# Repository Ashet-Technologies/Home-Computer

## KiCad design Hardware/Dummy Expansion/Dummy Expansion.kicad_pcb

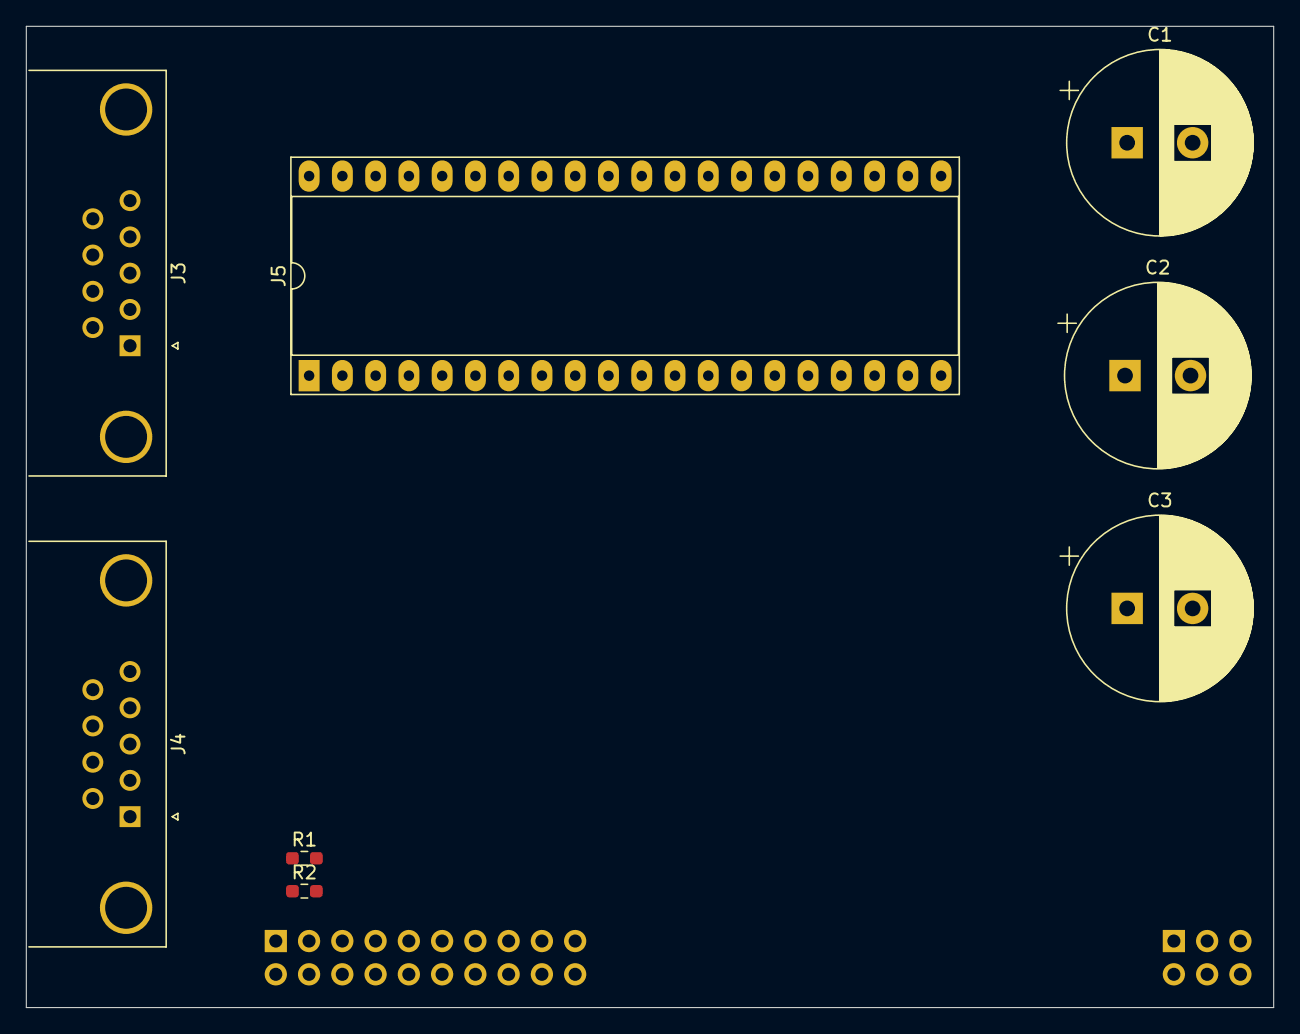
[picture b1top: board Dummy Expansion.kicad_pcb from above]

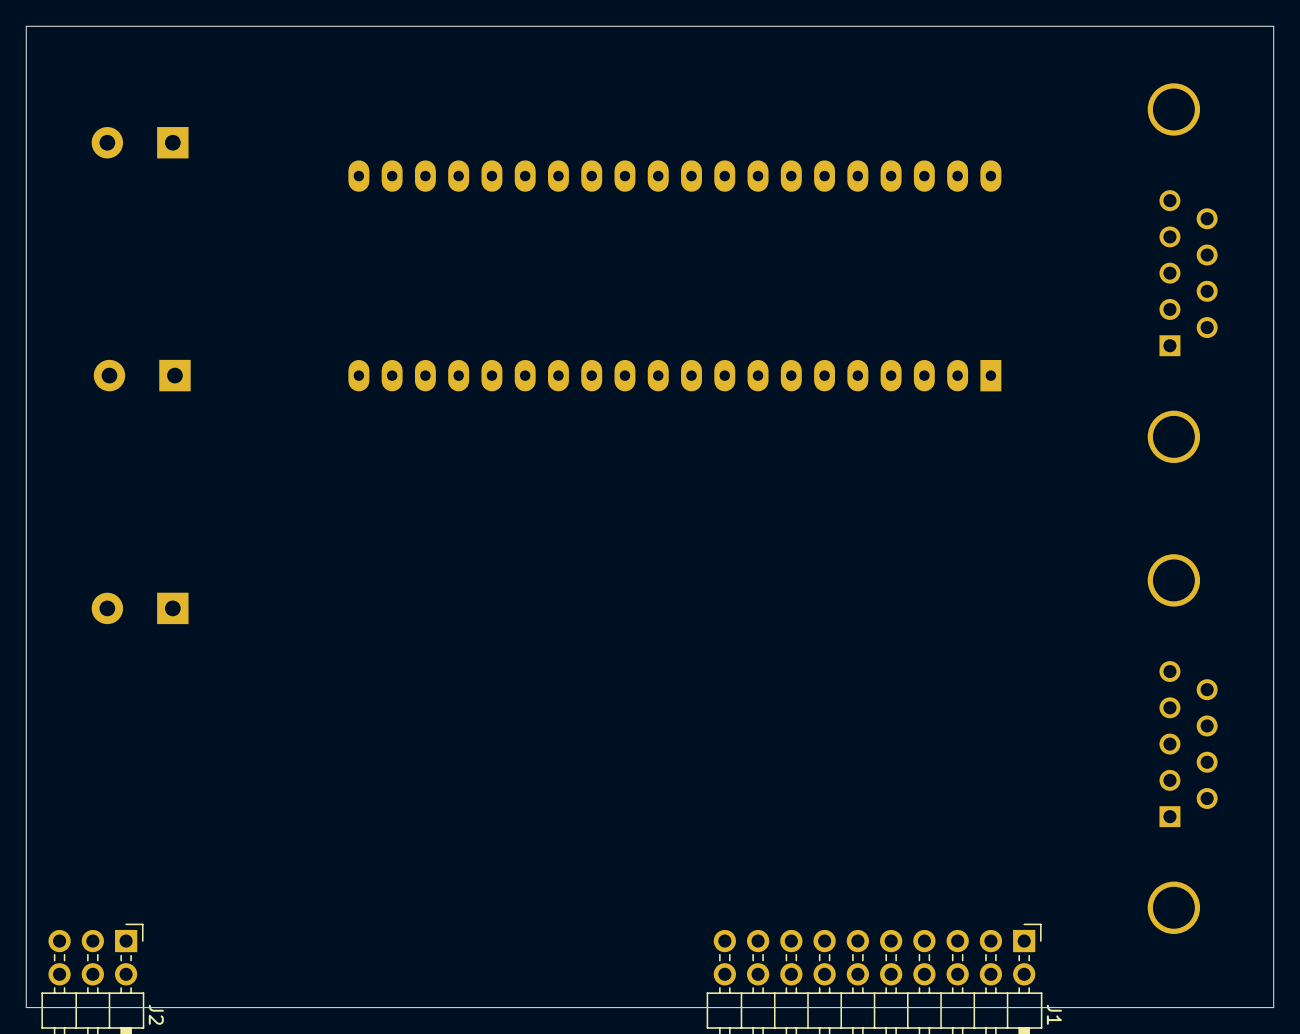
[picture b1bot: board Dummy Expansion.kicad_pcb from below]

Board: 2 copper layers, 95.2 x 74.9 mm, 10 parts (2 on the bottom side), 4 nets, no tracks yet.

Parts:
C1, C2, C3: C; CP_Radial_D14.0mm_P5.00mm
J1: Conn_02x10_Odd_Even; PinHeader_2x10_P2.54mm_Horizontal
J2: Conn_02x03_Counter_Clockwise; PinHeader_2x03_P2.54mm_Horizontal
J3, J4: DE9_Receptacle_MountingHoles; DSUB-9_Female_Horizontal_P2.77x2.84mm_EdgePinOffset4.94mm_H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
J5: Conn_02x20_Odd_Even; DIP-40_W15.24mm_Socket_LongPads
R1, R2: 10K; R_0603_1608Metric_Pad0.98x0.95mm_HandSolder

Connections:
+3V3: J1.19, R1.1, R2.1
/I2C_{SCL}: J1.4, R2.2
/I2C_{SDA}: J1.6, R1.2
GND: J1.2, J1.20, J2.1, J2.2, J2.3, J2.4, J2.5, J2.6

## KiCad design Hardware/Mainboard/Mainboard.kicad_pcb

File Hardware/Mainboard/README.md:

# Ashet Home Computer Mainboard

## Overview

- RP2350B as main CPU
- RP2350B as a debug probe
- Two 16 MiB flash chips
- 12 MHz Crystal for debug probe
- 4-port USB 1.1 HUB
- 10/100 Base-T/TX ethernet through ENC424J600
- 8 MB PSRAM (APS6404L-SQH-SN)
- 1.8V LDO for QSPI_IOVDD / PSRAM / Flash Chips

## Design Notes

- Attach debug probe to global I²S bus for both sniffing and controlling the system
- Debug probe must be able to reset the main CPU
- Debug probe can additionally drive global CLOCK_48MHZ so we can run the mainboard standalone without backplane
- Drive main CPU from CLOCK_48MHZ
- Drive debug probe through dedicated crystal
- Evaluate if debug probe can trigger the main cpu "boot over serial"
- Attach debug probe to main cpu flash directly
- Main CPU cannot be programmed through USB/UF2, but only through the debug probe
  - This must be as convenient as possible

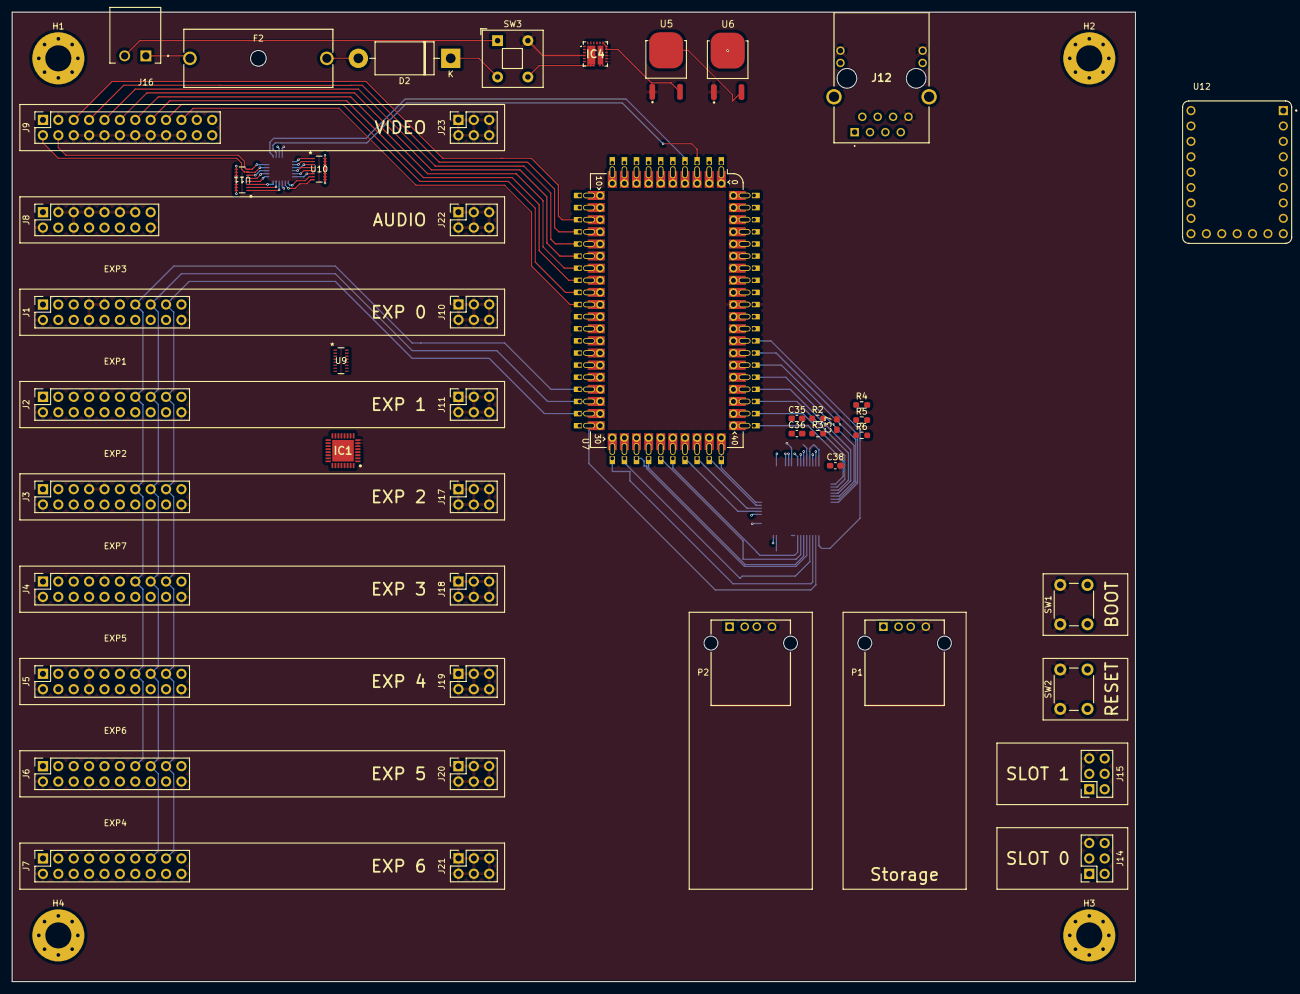
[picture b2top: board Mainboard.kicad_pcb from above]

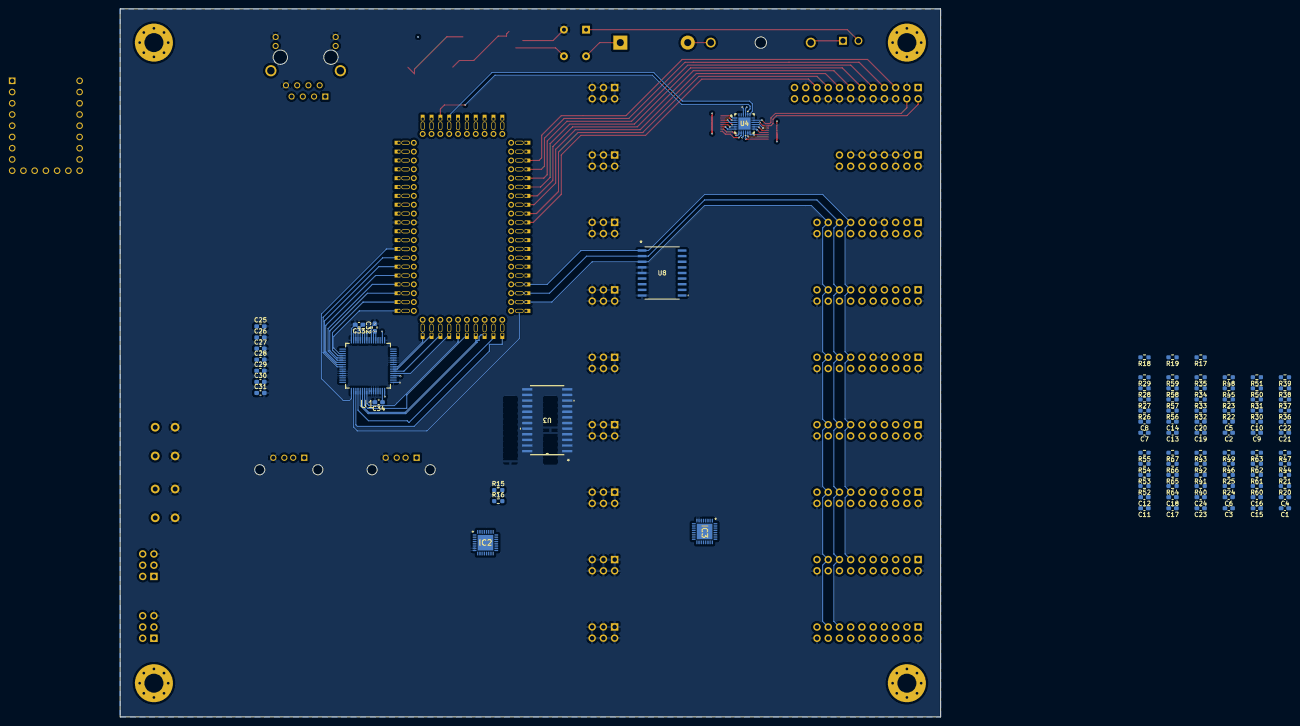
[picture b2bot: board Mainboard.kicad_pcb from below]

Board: 4 copper layers, 185.4 x 160.0 mm, 151 parts (93 on the bottom side), 159 nets.

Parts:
C1, C2, C3, C4, C5, C6, C7, C8, C9, C10, C11, C12, C13, C14, C15, C16, C17, C18, C19, C20, C21, C22, C23, C24: 22pF; C_0603_1608Metric_Pad1.08x0.95mm_HandSolder
C25, C26, C27, C28, C29, C30, C31: 100n; C_0603_1608Metric_Pad1.08x0.95mm_HandSolder
C32, C33: 1n; C_0603_1608Metric_Pad1.08x0.95mm_HandSolder
C34: 10uF; C_0603_1608Metric_Pad1.08x0.95mm_HandSolder
C35, C36: 6.8nF 10%; C_0603_1608Metric_Pad1.08x0.95mm_HandSolder
C37, C38: 10n; C_0603_1608Metric_Pad1.08x0.95mm_HandSolder
D2: 1N5822; D_DO-201AD_P15.24mm_Horizontal
EXP1, EXP2, EXP3, EXP4, EXP5, EXP6, EXP7: Expansion Card Preview
F2: 696107003002
H1, H2, H3, H4: MountingHole; MountingHole_4.3mm_M4_Pad_Via
IC1, IC2, IC3: TUSB2046BIRHBR
IC4: AOZ2261NQI-11; aoz2261ngl-11
J1, J2, J3, J4, J5, J6, J7: Conn_02x10_Odd_Even; PinSocket_2x10_P2.54mm_Vertical
J8: Conn_02x08_Odd_Even; PinSocket_2x08_P2.54mm_Vertical
J9: Conn_02x12_Odd_Even; PinSocket_2x12_P2.54mm_Vertical
J10, J11, J17, J18, J19, J20, J21, J22, J23: Conn_02x03_Counter_Clockwise; PinSocket_2x03_P2.54mm_Vertical
J12: ARJM11D7-009-AB-EW2
J14, J15: Conn_02x03_Odd_Even; PinSocket_2x03_P2.54mm_Vertical
J16: 1844210; combicon-1844210
P1, P2: USB-A1HSW6
R2, R3, R4, R5: 49.9 1%; R_0603_1608Metric_Pad0.98x0.95mm_HandSolder
R6: 10 1/12W 1%; R_0603_1608Metric_Pad0.98x0.95mm_HandSolder
R15, R16, R17, R18, R19: 10K; R_0603_1608Metric_Pad0.98x0.95mm_HandSolder
R20, R21, R22, R23, R24, R25, R26, R27, R30, R31, R32, R33, R36, R37, R40, R41, R52, R53, R56, R57, R60, R61, R64, R65: 27; R_0603_1608Metric_Pad0.98x0.95mm_HandSolder
R28, R29, R34, R35, R38, R39, R42, R43, R44, R45, R46, R47, R48, R49, R50, R51, R54, R55, R58, R59, R62, R63, R66, R67: 15K; R_0603_1608Metric_Pad0.98x0.95mm_HandSolder
SW1, SW2: SW_Push_Dual; SW_PUSH_6mm_H4.3mm
SW3: SW_DPST; SW_Push_2P1T_Toggle_CK_PVA1xxH1xxxxxxV2
U1: ENC624J600-I/PT; ENC624J600-I_PT
U3: CD74HC154M96
U4: TCA9548A; TCA9548ARGERQ1
U5, U6: AZ1084CD-3.3TRG1; AZ1084CD-3_3TRG1
U7: RP2350_Stamp_XL; RP2xxx_Stamp_XL_FlexyPin
U8: MCP23S08T-E/SO; MCP23S08T-E_SO
U9, U10, U11: YC248-JR-0710KL
U12: rp2040-zero

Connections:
+3V3: C25.1, C26.1, C27.1, C28.1, C29.1, C30.1, C31.1, C32.1, C33.1, IC1.3 (VCC_1), IC1.10 (~OVRCUR), IC1.14 (~OVRCUR2), IC1.18 (~OVRCUR3), IC1.22 (~OVRCUR4), IC1.25 (VCC_2), IC1.26 (~EXTMEM), IC2.3 (VCC_1), IC2.10 (~OVRCUR), IC2.14 (~OVRCUR2), IC2.18 (~OVRCUR3), IC2.22 (~OVRCUR4), IC2.25 (VCC_2), IC2.26 (~EXTMEM), IC3.3 (VCC_1), IC3.10 (~OVRCUR), IC3.14 (~OVRCUR2), IC3.18 (~OVRCUR3), IC3.22 (~OVRCUR4), IC3.25 (VCC_2), IC3.26 (~EXTMEM), J1.19, J2.7, J2.19, J3.8, J3.19, J4.7, J4.8, J4.19, J5.9, J5.19, J6.7, J6.9, J6.19, J7.8, J7.9, J7.19, J8.1, J9.1, J14.2, J15.2, R6.2, R15.1, R16.1, R17.1, R18.1, R19.1, U1.4 (VDDOSC), U1.18 (PSPCFG3), U1.21 (VDD_2), U1.22 (VDDPLL), U1.25 (VDDRX), U1.28 (VDDTX), U1.47 (VDD_3), U1.64 (VDD), U3.24 (VCC), U4.21 (VCC), U6.2 (VO), U8.6 (~RESET), U8.18 (VDD), U9.9 (R8), U9.10 (R7), U9.11 (R6), U9.12 (R5), U9.13 (R4), U9.14 (R3), U9.15 (R2), U9.16 (R1), U10.9 (R8), U10.10 (R7), U10.11 (R6), U10.12 (R5), U10.13 (R4), U10.14 (R3), U10.15 (R2), U10.16 (R1), U11.9 (R8), U11.10 (R7), U11.11 (R6), U11.12 (R5), U11.13 (R4), U11.14 (R3), U11.15 (R2), U11.16 (R1)
+5V: J1.1, J2.1, J3.1, J4.1, J5.1, J6.1, J7.1, J8.15, J9.23, J14.4, J15.4, P1.1 (VBUS), P2.1 (VBUS), U5.2 (VO), U6.3 (VI), U7.33 (5V), U12.23 (5V)
+6V: IC4.16 (LX_3), IC4.17 (LX_4), IC4.18 (LX_5), U5.3 (VI)
/DBG_{RXD}: U7.2 (GPIO1), U12.5 (GP4)
/DBG_{TXD}: U7.1 (GPIO0), U12.6 (GP5)
/Debug Subsystem/PROBE_SWCLK: U7.38 (SWCLK), U12.4 (GP3)
/Debug Subsystem/PROBE_SWDIO: U7.37 (SWDIO), U12.3 (GP2)
/Debug Subsystem/~BOOT: SW1.2, U7.40 (BOOTSEL)
/Debug Subsystem/~RESET: SW2.2, U7.39 (~RESET)
/Ethernet/ETH_{RX+}: C35.1, R2.1, U1.26 (TPIN+)
/Ethernet/ETH_{RX-}: C36.2, R3.1, U1.27 (TPIN-)
/Ethernet/ETH_{TX+}: J12.1 (TD+), R4.1, U1.30 (TPOUT+)
/Ethernet/ETH_{TX-}: J12.2 (TD-), R5.2, U1.31 (TPOUT-)
/Ethernet/PSP_{AD0}: U1.53 (AD0), U7.43 (GPIO32)
/Ethernet/PSP_{AD1}: U1.54 (AD1), U7.44 (GPIO33)
/Ethernet/PSP_{AD2}: U1.55 (AD2), U7.45 (GPIO34)
/Ethernet/PSP_{AD3}: U1.56 (AD3), U7.46 (GPIO35)
/Ethernet/PSP_{AD4}: U1.5 (AD4), U7.47 (GPIO36)
/Ethernet/PSP_{AD5}: U1.6 (AD5), U7.48 (GPIO37)
/Ethernet/PSP_{AD6}: U1.7 (AD6), U7.49 (GPIO38)
/Ethernet/PSP_{AD7}: U1.8 (AD7), U7.50 (GPIO39)
/Ethernet/PSP_{AD8}: U1.35 (AD8), U7.51 (GPIO40)
/Ethernet/PSP_{AD9}: U1.36 (AD9), U7.52 (GPIO41)
/Ethernet/PSP_{AD10}: U1.37 (AD10), U7.53 (GPIO42)
/Ethernet/PSP_{AD11}: U1.38 (AD11), U7.54 (GPIO43)
/Ethernet/PSP_{AD12}: U1.39 (AD12), U7.55 (GPIO44)
/Ethernet/PSP_{AD13}: U1.40 (AD13), U7.56 (GPIO45)
/Ethernet/PSP_{AD14}: U1.41 (AD14), U7.57 (GPIO46)
/Ethernet/PSP_{AL}: U1.52 (SCK/AL/PSPCFG4), U7.42 (GPIO31)
/Ethernet/PSP_{CS}: U1.49 (~CS/CS), U7.58 (GPIO47)
/Ethernet/PSP_{RD}: U1.51 (SI/RD/R~W), U7.41 (GPIO30)
/Ethernet/PSP_{WR}: U1.50 (SO/WR/WRL/EN/BOSEL), U7.30 (GPIO29)
/Expansion Subsystem/D0_{D+}: IC1.1 (DP0), R57.1, R58.2
/Expansion Subsystem/D0_{D-}: IC1.2 (DM0), R56.1, R59.2
/Expansion Subsystem/D1_{D+}: IC3.1 (DP0), R33.1, R34.2
/Expansion Subsystem/I2C0_{SCL}: U4.2 (SC0), U10.2 (R2)
/Expansion Subsystem/I2C0_{SDA}: U4.1 (SD0), U10.1 (R1)
/Expansion Subsystem/I2C1_{SCL}: U4.4 (SC1), U10.4 (R4)
/Expansion Subsystem/I2C1_{SDA}: U4.3 (SD1), U10.3 (R3)
/Expansion Subsystem/I2C2_{SCL}: U4.6 (SC2), U10.6 (R6)
/Expansion Subsystem/I2C2_{SDA}: U4.5 (SD2), U10.5 (R5)
/Expansion Subsystem/I2C3_{SCL}: U4.8 (SC3), U10.8 (R8)
/Expansion Subsystem/I2C3_{SDA}: U4.7 (SD3), U10.7 (R7)
/Expansion Subsystem/I2C4_{SCL}: U4.11 (SC4), U11.2 (R2)
/Expansion Subsystem/I2C4_{SDA}: U4.10 (SD4), U11.1 (R1)
/Expansion Subsystem/I2C5_{SCL}: U4.13 (SC5), U11.4 (R4)
/Expansion Subsystem/I2C5_{SDA}: U4.12 (SD5), U11.3 (R3)
/Expansion Subsystem/I2C6_{SCL}: U4.14 (SD6), U11.5 (R5)
/Expansion Subsystem/I2C6_{SDA}: U4.15 (SC6), U11.6 (R6)
/Expansion Subsystem/IRQ_{0}: J1.10, U8.10 (GP0), U9.8 (R8)
/Expansion Subsystem/IRQ_{1}: J2.10, U8.11 (GP1), U9.7 (R7)
/Expansion Subsystem/IRQ_{2}: J3.10, U8.12 (GP2), U9.6 (R6)
/Expansion Subsystem/IRQ_{3}: J4.10, U8.13 (GP3), U9.5 (R5)
/Expansion Subsystem/IRQ_{4}: J5.10, U8.14 (GP4), U9.4 (R4)
/Expansion Subsystem/IRQ_{5}: J6.10, U8.15 (GP5), U9.3 (R3)
/Expansion Subsystem/IRQ_{6}: J7.10, U8.16 (GP6), U9.2 (R2)
/Expansion Subsystem/IRQ_{7}: U8.17 (GP7), U9.1 (R1)
/Expansion Subsystem/SPI_{CS0}: J1.11, U3.2 (~Y1)
/Expansion Subsystem/SPI_{CS1}: J1.12, U3.3 (~Y2)
/Expansion Subsystem/SPI_{CS2}: J2.11, U3.4 (~Y3)
/Expansion Subsystem/SPI_{CS3}: J2.12, U3.5 (~Y4)
/Expansion Subsystem/SPI_{CS4}: J3.11, U3.6 (~Y5)
/Expansion Subsystem/SPI_{CS5}: J3.12, U3.7 (~Y6)
/Expansion Subsystem/SPI_{CS6}: J4.11, U3.8 (~Y7)
/Expansion Subsystem/SPI_{CS7}: J4.12, U3.9 (~Y8)
/Expansion Subsystem/SPI_{CS8}: J5.11, U3.10 (~Y9)
/Expansion Subsystem/SPI_{CS9}: J5.12, U3.11 (~Y10)
/Expansion Subsystem/SPI_{CS10}: J6.11, U3.13 (~Y11)
/Expansion Subsystem/SPI_{CS11}: J6.12, U3.14 (~Y12)
/Expansion Subsystem/SPI_{CS12}: J7.11, U3.15 (~Y13)
/Expansion Subsystem/SPI_{CS13}: J7.12, U3.16 (~Y14), U3.17 (~Y15), U8.7 (~CS)
/Expansion Subsystem/USB0_{D+}: J1.3, R60.1, R63.2
/Expansion Subsystem/USB0_{D-}: J1.5, R61.1, R62.2
/Expansion Subsystem/USB1_{D+}: J2.3, R36.1, R39.2
/Expansion Subsystem/USB1_{D-}: J2.5, R37.1, R38.2
/Expansion Subsystem/USB2_{D+}: J3.3, R30.1, R51.2
/Expansion Subsystem/USB2_{D-}: J3.5, R31.1, R50.2
/Expansion Subsystem/USB3_{D+}: J4.3, R20.1, R47.2
/Expansion Subsystem/USB3_{D-}: J4.5, R21.1, R44.2
/Expansion Subsystem/USB4_{D+}: J5.3, R64.1, R67.2
/Expansion Subsystem/USB4_{D-}: J5.5, R65.1, R66.2
/Expansion Subsystem/USB5_{D+}: J6.3, R40.1, R43.2
/Expansion Subsystem/USB5_{D-}: J6.5, R41.1, R42.2
/Expansion Subsystem/USB6_{D+}: J7.3, R52.1, R55.2
/Expansion Subsystem/USB6_{D-}: J7.5, R53.1, R54.2
/Expansion Subsystem/USB Hub x5/USB Terminator1/HUB_{D+}: C10.1, IC1.20 (DP3), R30.2
/Expansion Subsystem/USB Hub x5/USB Terminator1/HUB_{D-}: C9.1, IC1.19 (DM3), R31.2
/Expansion Subsystem/USB Hub x5/USB Terminator2/HUB_{D+}: C16.1, IC1.16 (DP2), R60.2
/Expansion Subsystem/USB Hub x5/USB Terminator2/HUB_{D-}: C15.1, IC1.15 (DM2), R61.2
/Expansion Subsystem/USB Hub x5/USB Terminator3/HUB_{D+}: C22.1, IC1.12 (DP1), R36.2
/Expansion Subsystem/USB Hub x5/USB Terminator3/HUB_{D-}: C21.1, IC1.11 (DM1), R37.2
/Expansion Subsystem/USB Hub x5/USB Terminator/HUB_{D+}: C4.1, IC1.24 (DP4), R20.2
/Expansion Subsystem/USB Hub x5/USB Terminator/HUB_{D-}: C1.1, IC1.23 (DM4), R21.2
/Expansion Subsystem/USB Hub x5/~RESET: IC1.4 (~RESET), R18.2
/Expansion Subsystem/USB Hub x6/D3_{D+}: R24.1, R49.2
/Expansion Subsystem/USB Hub x6/D3_{D-}: R25.1, R46.2
/Expansion Subsystem/USB Hub x6/USB Terminator1/HUB_{D+}: C12.1, IC3.20 (DP3), R52.2
/Expansion Subsystem/USB Hub x6/USB Terminator1/HUB_{D-}: C11.1, IC3.19 (DM3), R53.2
/Expansion Subsystem/USB Hub x6/USB Terminator2/HUB_{D+}: C18.1, IC3.16 (DP2), R64.2
/Expansion Subsystem/USB Hub x6/USB Terminator2/HUB_{D-}: C17.1, IC3.15 (DM2), R65.2
/Expansion Subsystem/USB Hub x6/USB Terminator3/HUB_{D+}: C24.1, IC3.12 (DP1), R40.2
/Expansion Subsystem/USB Hub x6/USB Terminator3/HUB_{D-}: C23.1, IC3.11 (DM1), R41.2
/Expansion Subsystem/USB Hub x6/USB Terminator/HUB_{D+}: C6.1, IC3.24 (DP4), R24.2
/Expansion Subsystem/USB Hub x6/USB Terminator/HUB_{D-}: C3.1, IC3.23 (DM4), R25.2
/Expansion Subsystem/USB Hub x6/~RESET: IC3.4 (~RESET), R19.2
/HSTX_{0}: J9.5, U7.13 (GPIO12)
/HSTX_{1}: J9.7, U7.14 (GPIO13)
/HSTX_{2}: J9.9, U7.15 (GPIO14)
/HSTX_{3}: J9.11, U7.16 (GPIO15)
/HSTX_{4}: J9.13, U7.17 (GPIO16)
/HSTX_{5}: J9.15, U7.18 (GPIO17)
/HSTX_{6}: J9.17, U7.19 (GPIO18)
/HSTX_{7}: J9.19, U7.20 (GPIO19)
/I2C_{SCL}: U4.19 (SCL), U7.4 (GPIO3)
/I2C_{SDA}: U4.20 (SDA), U7.3 (GPIO2)
/I2C_{~RESET}: U4.24 (~RESET), U7.10 (GPIO9)
/I2S_{IN}: J8.14, U7.24 (GPIO23)
/I2S_{LRCK}: J8.8, U7.22 (GPIO21)
/I2S_{MCK}: J8.4, U7.26 (GPIO25)
/I2S_{OUT}: J8.12, U7.23 (GPIO22)
/I2S_{SCK}: J8.10, U7.25 (GPIO24)
/SPI_{CSi0}: U3.23 (A0), U7.5 (GPIO4)
/SPI_{CSi1}: U3.22 (A1), U7.6 (GPIO5)
/SPI_{CSi2}: U3.21 (A2), U7.7 (GPIO6)
/SPI_{CSi3}: U3.20 (A3), U7.8 (GPIO7)
/SPI_{MISO}: J1.17, J2.17, J3.17, J4.17, J5.17, J6.17, J7.17, U7.29 (GPIO28), U8.3 (SO)
/SPI_{MOSI}: J1.15, J2.15, J3.15, J4.15, J5.15, J6.15, J7.15, U7.28 (GPIO27), U8.2 (SI)
/SPI_{SCK}: J1.13, J2.13, J3.13, J4.13, J5.13, J6.13, J7.13, U7.27 (GPIO26), U8.1 (SCK)
/SYS_{SCL}: J9.4, J14.1, J15.1, R16.2, U4.17 (SC7), U11.8 (R8)
/SYS_{SDA}: J9.2, J14.3, J15.3, R15.2, U4.16 (SD7), U11.7 (R7)
/USB Subsystem/D1_{D-}: R32.1, R35.2
/USB Subsystem/D2_{D+}: P1.3 (D+), R26.1, R29.2
/USB Subsystem/D2_{D-}: P1.2 (D-), R27.1, R28.2
/USB Subsystem/D3_{D+}: P2.3 (D+), R22.1, R48.2
/USB Subsystem/D3_{D-}: P2.2 (D-), R23.1, R45.2
/USB Subsystem/USB Hub x4/USB Terminator1/HUB_{D+}: C8.1, IC2.20 (DP3), R26.2
/USB Subsystem/USB Hub x4/USB Terminator1/HUB_{D-}: C7.1, IC2.19 (DM3), R27.2
/USB Subsystem/USB Hub x4/USB Terminator2/HUB_{D+}: C14.1, IC2.16 (DP2), R56.2
/USB Subsystem/USB Hub x4/USB Terminator2/HUB_{D-}: C13.1, IC2.15 (DM2), R57.2
/USB Subsystem/USB Hub x4/USB Terminator3/HUB_{D+}: C20.1, IC2.12 (DP1), R32.2
/USB Subsystem/USB Hub x4/USB Terminator3/HUB_{D-}: C19.1, IC2.11 (DM1), R33.2
/USB Subsystem/USB Hub x4/USB Terminator/HUB_{D+}: C5.1, IC2.24 (DP4), R22.2
/USB Subsystem/USB Hub x4/USB Terminator/HUB_{D-}: C2.1, IC2.23 (DM4), R23.2
/USB Subsystem/USB Hub x4/~RESET: IC2.4 (~RESET), R17.2
/USB_{D+}: IC2.1 (DP0), U7.36 (USB_D+)
/USB_{D-}: IC2.2 (DM0), U7.35 (USB_D-)
/~IRQ_{ETH}: U1.34 (~INT/SPISEL), U7.12 (GPIO11)
/~IRQ_{EXT}: U7.11 (GPIO10), U8.8 (INT)
GND: C1.2, C2.2, C3.2, C4.2, C5.2, C6.2, C7.2, C8.2, C9.2, C10.2, C11.2, C12.2, C13.2, C14.2, C15.2, C16.2, C17.2, C18.2, C19.2, C20.2, C21.2, C22.2, C23.2, C24.2, C25.2, C26.2, C27.2, C28.2, C29.2, C30.2, C31.2, C32.2, C33.2, C34.2, C37.2, C38.2, IC1.6 (EEDATA/GANGED), IC1.7 (GND_1), IC1.8 (BUSPWR), IC1.28 (GND_2), IC1.33 (EP), IC2.6 (EEDATA/GANGED), IC2.7 (GND_1), IC2.8 (BUSPWR), IC2.28 (GND_2), IC2.33 (EP), IC3.6 (EEDATA/GANGED), IC3.7 (GND_1), IC3.8 (BUSPWR), IC3.28 (GND_2), IC3.33 (EP), IC4.4 (AGND), IC4.12 (PGND_1), IC4.13 (PGND_2), IC4.14 (PGND_3), IC4.15 (PGND_4), J1.2, J1.7, J1.8, J1.9, J1.20, J2.2, J2.8, J2.9, J2.20, J3.2, J3.7, J3.9, J3.20, J4.2, J4.9, J4.20, J5.2, J5.7, J5.8, J5.20, J6.2, J6.8, J6.20, J7.2, J7.7, J7.20, J8.2, J8.3, J8.5, J8.6, J8.7, J8.9, J8.11, J8.13, J8.16, J9.3, J9.6, J9.8, J9.10, J9.12, J9.14, J9.16, J9.18, J9.20, J9.21, J10.1, J10.2, J10.3, J10.4, J10.5, J10.6, J11.1, J11.2, J11.3, J11.4, J11.5, J11.6, J12.8 (GND), J12.10, J12.12, J14.5, J15.5, J17.1, J17.2, J17.3, J17.4, J17.5, J17.6, J18.1, J18.2, J18.3, J18.4, J18.5, J18.6, J19.1, J19.2, J19.3, J19.4, J19.5, J19.6, J20.1, J20.2, J20.3, J20.4, J20.5, J20.6, J21.1, J21.2, J21.3, J21.4, J21.5, J21.6, J22.1, J22.2, J22.3, J22.4, J22.5, J22.6, J23.1, J23.2, J23.3, J23.4, J23.5, J23.6, P1.4 (GND), P2.4 (GND), R28.1, R29.1, R34.1, R35.1, R38.1, R39.1, R42.1, R43.1, R44.1, R45.1, R46.1, R47.1, R48.1, R49.1, R50.1, R51.1, R54.1, R55.1, R58.1, R59.1, R62.1, R63.1, R66.1, R67.1, SW1.1, SW2.1, SW3.2, U1.1 (VSSOSC), U1.9 (A5), U1.10 (A6), U1.11 (A7), U1.12 (A8), U1.13 (A9), U1.17 (PSPCFG2), U1.19 (A10), U1.20 (A11), U1.23 (VSSPLL), U1.24 (VSSRX), U1.29 (VSSTX1), U1.32 (VSSTX), U1.42 (AD15), U1.43 (A12), U1.44 (A13), U1.45 (A14/PSPCFG1), U1.46 (VSS_2), U1.57 (A0), U1.58 (A1), U1.59 (A2), U1.60 (A3), U1.61 (A4), U1.62 (VSS), U3.12 (GND), U3.18 (~E1), U3.19 (~E2), U4.9 (GND), U4.18 (A2), U4.22 (A0), U4.23 (A1), U4.25 (GND), U5.1 (GND), U6.1 (GND), U7.31 (GND), U8.4 (A1), U8.5 (A0), U8.9 (VSS), U12.22 (GND)
unnamed: D2.2 (A), F2.2
unnamed: D2.1 (K), SW3.3
unnamed: F2.1, J16.1
unnamed: C37.1, J12.5 (CR), R2.2, R3.2
unnamed: C38.1, J12.4 (CT), R4.2, R5.1, R6.1
unnamed: C35.2, J12.3 (RD+)
unnamed: C36.1, J12.6 (RD-)
unnamed: J16.2, SW3.1
unnamed: C34.1, U1.63 (VCAP)
VCC: IC4.7 (IN_1), IC4.8 (IN_2), IC4.9 (IN_3), SW3.4
